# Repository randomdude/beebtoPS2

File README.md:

Here's a project to enable you to use a modern (ish) PS/2 keyboard on your BBC Micro.

It is built around a Xilinx XC95144XL CPLD. Originally it was in a XC9572, which I love because they are 5v tolerant and also available in PLCC package. However, the design outgrew that chip, and so the TQFP XC95144XL is now required.

The board itself is pretty simple. There's a comparator and a couple octal buffers to sequence power, since otherwise the IO lines may go higher than vcc during power-up, by enough that the CPLD can be damaged. Then there's just the PS/2 socket for your keyboard, 8 debug LEDs, and some DIP switches (which map to the BBC micro's configuration bits). 

Please let me know if you build one, or find this interesting!

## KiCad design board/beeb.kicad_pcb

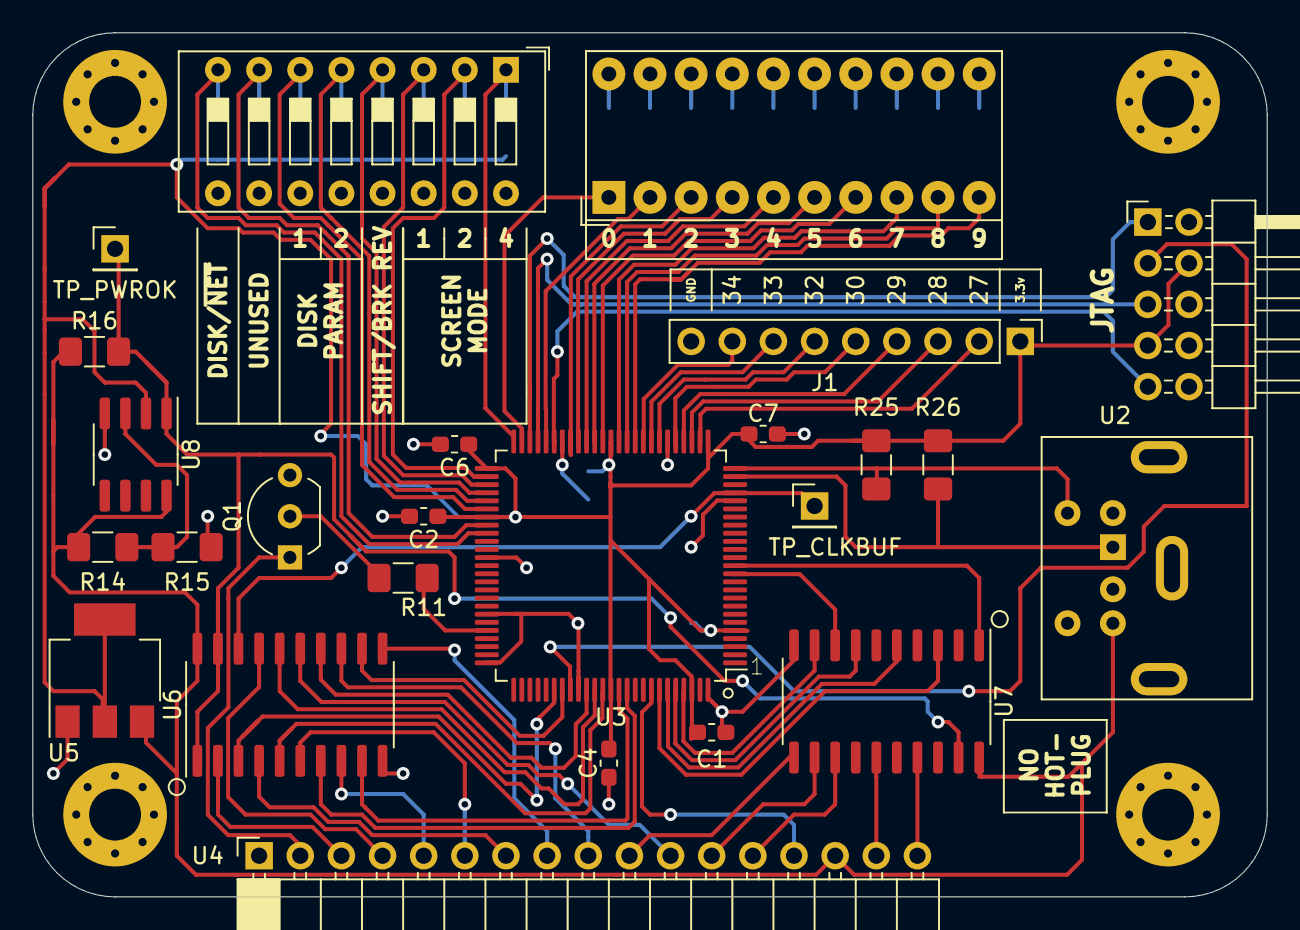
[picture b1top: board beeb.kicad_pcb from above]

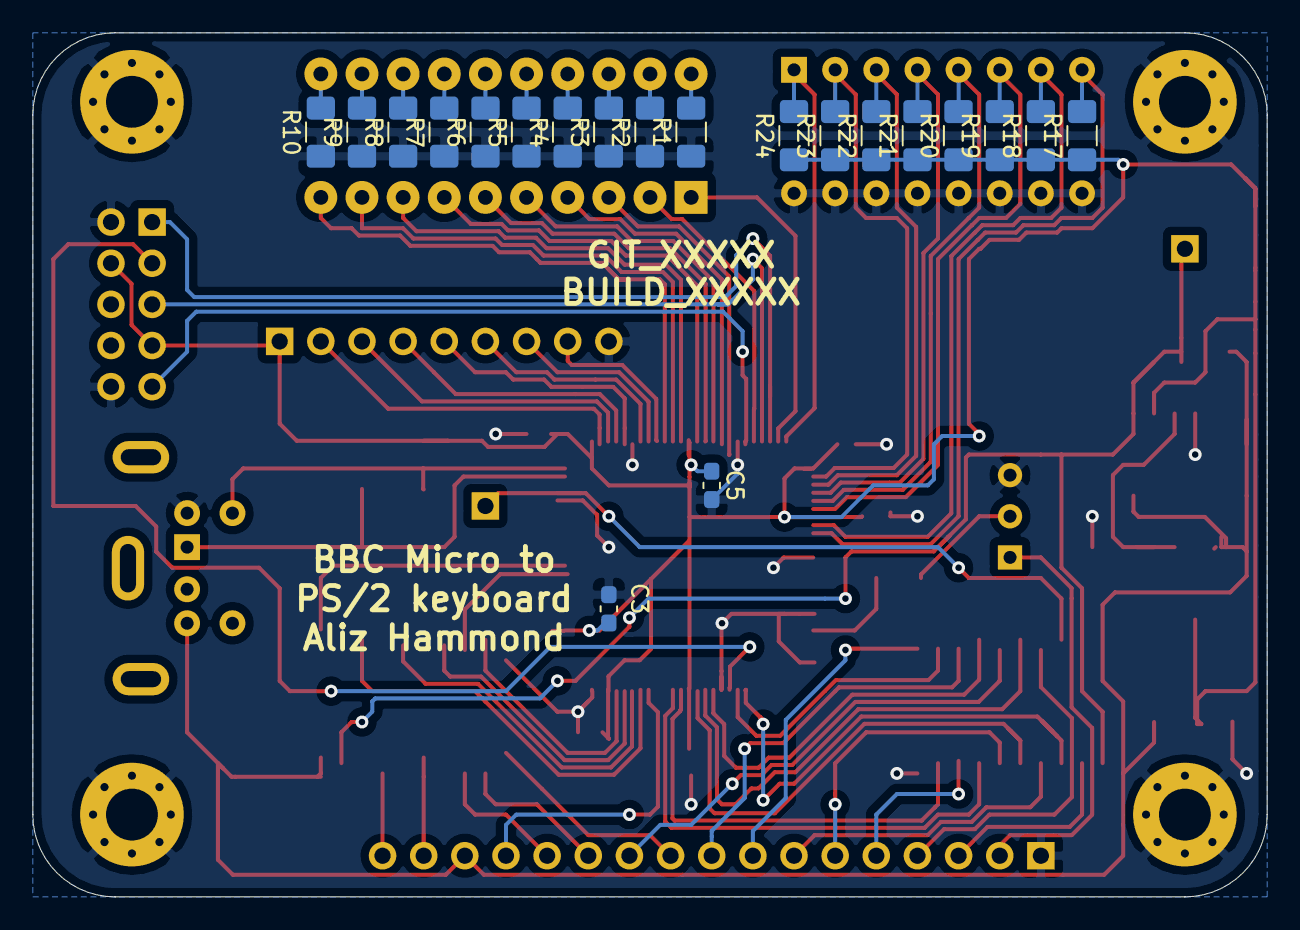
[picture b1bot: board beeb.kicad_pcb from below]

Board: 2 copper layers, 76.2 x 53.3 mm, 49 parts (20 on the bottom side), 77 nets.

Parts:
BAR1: HDSP-4830_2; HDSP-4830
C1, C2, C3, C4, C5, C6, C7: C; C_0603_1608Metric_Pad1.05x0.95mm_HandSolder
H1, H2, H3, H4: MountingHole_Pad; MountingHole_3.2mm_M3_Pad_Via
J1: Conn_01x09_Male; PinHeader_1x09_P2.54mm_Vertical
J2: AVR-JTAG-10; PinHeader_2x05_P2.54mm_Horizontal
Q1: BC337; TO-92_Inline_Wide
R1, R2, R3, R4, R5, R6, R7, R8, R9, R10, R16, R17, R18, R19, R20, R21, R22, R23, R24, R25, R26: 10K; R_1206_3216Metric_Pad1.42x1.75mm_HandSolder
R11: 220; R_1206_3216Metric_Pad1.42x1.75mm_HandSolder
R14, R15: R; R_1206_3216Metric_Pad1.42x1.75mm_HandSolder
SW1: SW_DIP_x08; SW_DIP_SPSTx08_Slide_9.78x22.5mm_W7.62mm_P2.54mm
TP1: TP_PWROK; PinHeader_1x01_P2.54mm_Vertical
TP2: TP_CLKBUF; PinHeader_1x01_P2.54mm_Vertical
U2: ps2; Connector_Mini-DIN_Female_6Pin_2rows
U3: XC95144XL-TQ100; TQFP-100_14x14mm_P0.5mm
U4: beebKB; PinSocket_1x17_P2.54mm_Horizontal
U5: LM1117-3.3; SOT-223-3_TabPin2
U6, U7: 74LS244_Split; beeb_SO-20_5.3x12.6mm_P1.27mm
U8: LM2903; SOP-8_3.76x4.96mm_P1.27mm

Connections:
+3V3: C1.1, C2.1, C3.1, C4.1, C5.1, C6.1, C7.1, J1.1, J2.4, J2.7, R17.1, R18.1, R19.1, R20.1, R21.1, R22.1, R23.1, R24.1, R25.1, R26.1, U3.5, U3.26, U3.38, U3.51, U3.57, U3.88, U3.98, U5.2, U8.2
+5V: R14.1, R16.1, U2.4, U4.15, U5.3, U6.20, U7.20, U8.8
/BEEBCLK: U4.3, U6.2
/BEEBCLK_BUF: TP2.1, U3.22, U6.18
/CA2: U3.93, U4.14
/CB: U4.4, U6.17
/CB_BUF: U3.81, U6.3
/COL0: U4.5, U6.8
/COL0_BUF: U3.82, U6.12
/COL1: U4.6, U6.6
/COL1_BUF: U3.85, U6.14
/COL2: U4.7, U6.4
/COL2_BUF: U3.86, U6.16
/LED1: BAR1.1, U3.49
/LED2: BAR1.2, U3.46
/LED3: BAR1.3, U3.43
/LED4: BAR1.4, U3.42
/LED5: BAR1.5, U3.41
/LED6: BAR1.6, U3.40
/LED7: BAR1.7, U3.39
/LED8: BAR1.8, U3.37
/LED9: BAR1.9, U3.36
/LED10: BAR1.10, U3.35
/LED_CAPS_BUF: U3.94, U7.3
/LED_CAS_BUF: U3.96, U7.7
/LED_SHIFT_BUF: U3.95, U7.5
/PS2CLK_A: R25.2, U2.5, U3.25
/PS2DATA_A: R26.2, U2.1, U3.24
/PWROK: R16.2, TP1.1, U6.1, U6.19, U7.19, U8.1
/ROW0: U4.8, U6.11
/ROW0_BUF: U3.89, U6.9
/ROW1: U4.9, U6.13
/ROW1_BUF: U3.90, U6.7
/ROW2: U4.10, U7.11
/ROW2_BUF: U3.97, U7.9
/ROW3: U4.11, U6.15
/ROW3_BUF: U3.87, U6.5
/RST: R11.1, U3.71
/TCK: J2.1, U3.48
/TDI: J2.9, U3.45
/TDO: J2.3, U3.83
/TMS: J2.5, U3.47
/W: U4.12, U7.12
/W_BUF: U3.12, U7.8
/W_EN: U3.13, U7.1
GND: C1.2, C2.2, C3.2, C4.2, C5.2, C6.2, C7.2, H1.1, H2.1, H3.1, H4.1, J1.9, J2.2, J2.10, Q1.3, R1.1, R2.1, R3.1, R4.1, R5.1, R6.1, R7.1, R8.1, R9.1, R10.1, R15.2, SW1.9, SW1.10, SW1.11, SW1.12, SW1.13, SW1.14, SW1.15, SW1.16, U2.3, U3.21, U3.31, U3.44, U3.62, U3.69, U3.75, U3.84, U3.100, U4.1, U5.1, U6.10, U7.10, U8.4
unnamed: BAR1.11, R10.2
unnamed: BAR1.12, R9.2
unnamed: BAR1.13, R8.2
unnamed: BAR1.14, R7.2
unnamed: BAR1.15, R6.2
unnamed: BAR1.16, R5.2
unnamed: BAR1.17, R4.2
unnamed: BAR1.18, R3.2
unnamed: BAR1.19, R2.2
unnamed: BAR1.20, R1.2
unnamed: J1.2, U3.27
unnamed: J1.3, U3.28
unnamed: J1.4, U3.29
unnamed: J1.5, U3.30
unnamed: J1.6, U3.32
unnamed: J1.7, U3.33
unnamed: J1.8, U3.34
unnamed: Q1.1, U4.2
unnamed: Q1.2, R11.2
unnamed: R14.2, R15.1, U8.3
unnamed: R17.2, SW1.8, U3.59
unnamed: R18.2, SW1.7, U3.58
unnamed: R19.2, SW1.6, U3.56
unnamed: R20.2, SW1.5, U3.55
unnamed: R21.2, SW1.4, U3.54
unnamed: R22.2, SW1.3, U3.53
unnamed: R23.2, SW1.2, U3.52
unnamed: R24.2, SW1.1, U3.50
unnamed: U4.13, U7.13
unnamed: U4.16, U7.15
unnamed: U4.17, U7.17

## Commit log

2021-06-26 Add ISE project files
2021-06-26 add .ngc file
2021-06-26 add script to generate prj files
2021-06-26 observe file type when generating .prj
2021-06-26 create .prj for each test
2021-06-27 Update test
2021-06-27 don't use implemnetation files as test files
2021-06-27 Move test running to python file
2021-06-27 Make test fail to test jenkins
2021-06-27 Remove test assert
2021-06-27 Add jenkinsfile
2021-06-27 fix jenkinsfile syntax
2021-06-27 fix jenkinsfile typo
2021-06-27 look for PCB in board/ dir
2021-06-27 Widen clearance around jtag vias
2021-06-27 remove spur trace
2021-07-22 Add ps/2 socket footprint from github. Add USB socket via WIT122 IC.
2021-07-22 Change USB socket footprint, impedence match usb p/n and ps2 clk/data
2021-08-10 hack until working
2021-08-10 tweak hole placement
2021-08-23 connect CPLD vio to 3.3v, change 3.3v reg to lm1117t
2021-08-23 fix unconnected pad
2021-08-25 Connect jtag connector to 3v3
2021-08-25 Update silkscreen
2021-09-01 fix some tests, change debug LEDs
2021-09-03 tidy up vhdl testbench
2021-09-03 Wait only four beeb-clocks before starting a new ps/2 byte
2021-09-03 Add 'fastclk' fast async clock for sampling ps2 clock
2021-09-03 xml escape some bits
2021-09-03 remove unused vars, further attempts to beat the beast of metastability
2021-09-04 better cleaning of error messages for test XML
2021-09-04 xml escape test failure type
2021-09-04 Mark testVectors.vhd as required for implimentation
2021-09-04 add forgotten file
2021-09-05 improve test result generation
2021-09-05 Correct fastclk
2021-09-05 add gitignore with cpld stuff
2021-09-05 reformat spaces to tabs
2021-10-17 add wit122uh example dox
2021-10-17 Make it work
2021-10-17 add dual usb socket diagram
2021-10-17 Move silk, correct beebkb symbol
2021-10-17 add forgotten test files
2021-10-21 Remove USB connector, move JTAG connector, mess about
2021-10-22 Add reset line, remov vref pot
2021-10-22 remove references to usb lines
2021-11-03 Connect U8 to power/gnd, change U6 and U7 footprint, add TP_CLKBUF, tidy
2021-11-04 Tidy schematic a little
2021-11-04 correct inverted dip sw
2021-11-16 Yay, it works now!
2021-11-16 add README
2021-11-16 reformat
